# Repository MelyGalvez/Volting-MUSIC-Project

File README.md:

# Volting Music Project
Extension of Volting Music project to a more immersive environnement in Tongji University.

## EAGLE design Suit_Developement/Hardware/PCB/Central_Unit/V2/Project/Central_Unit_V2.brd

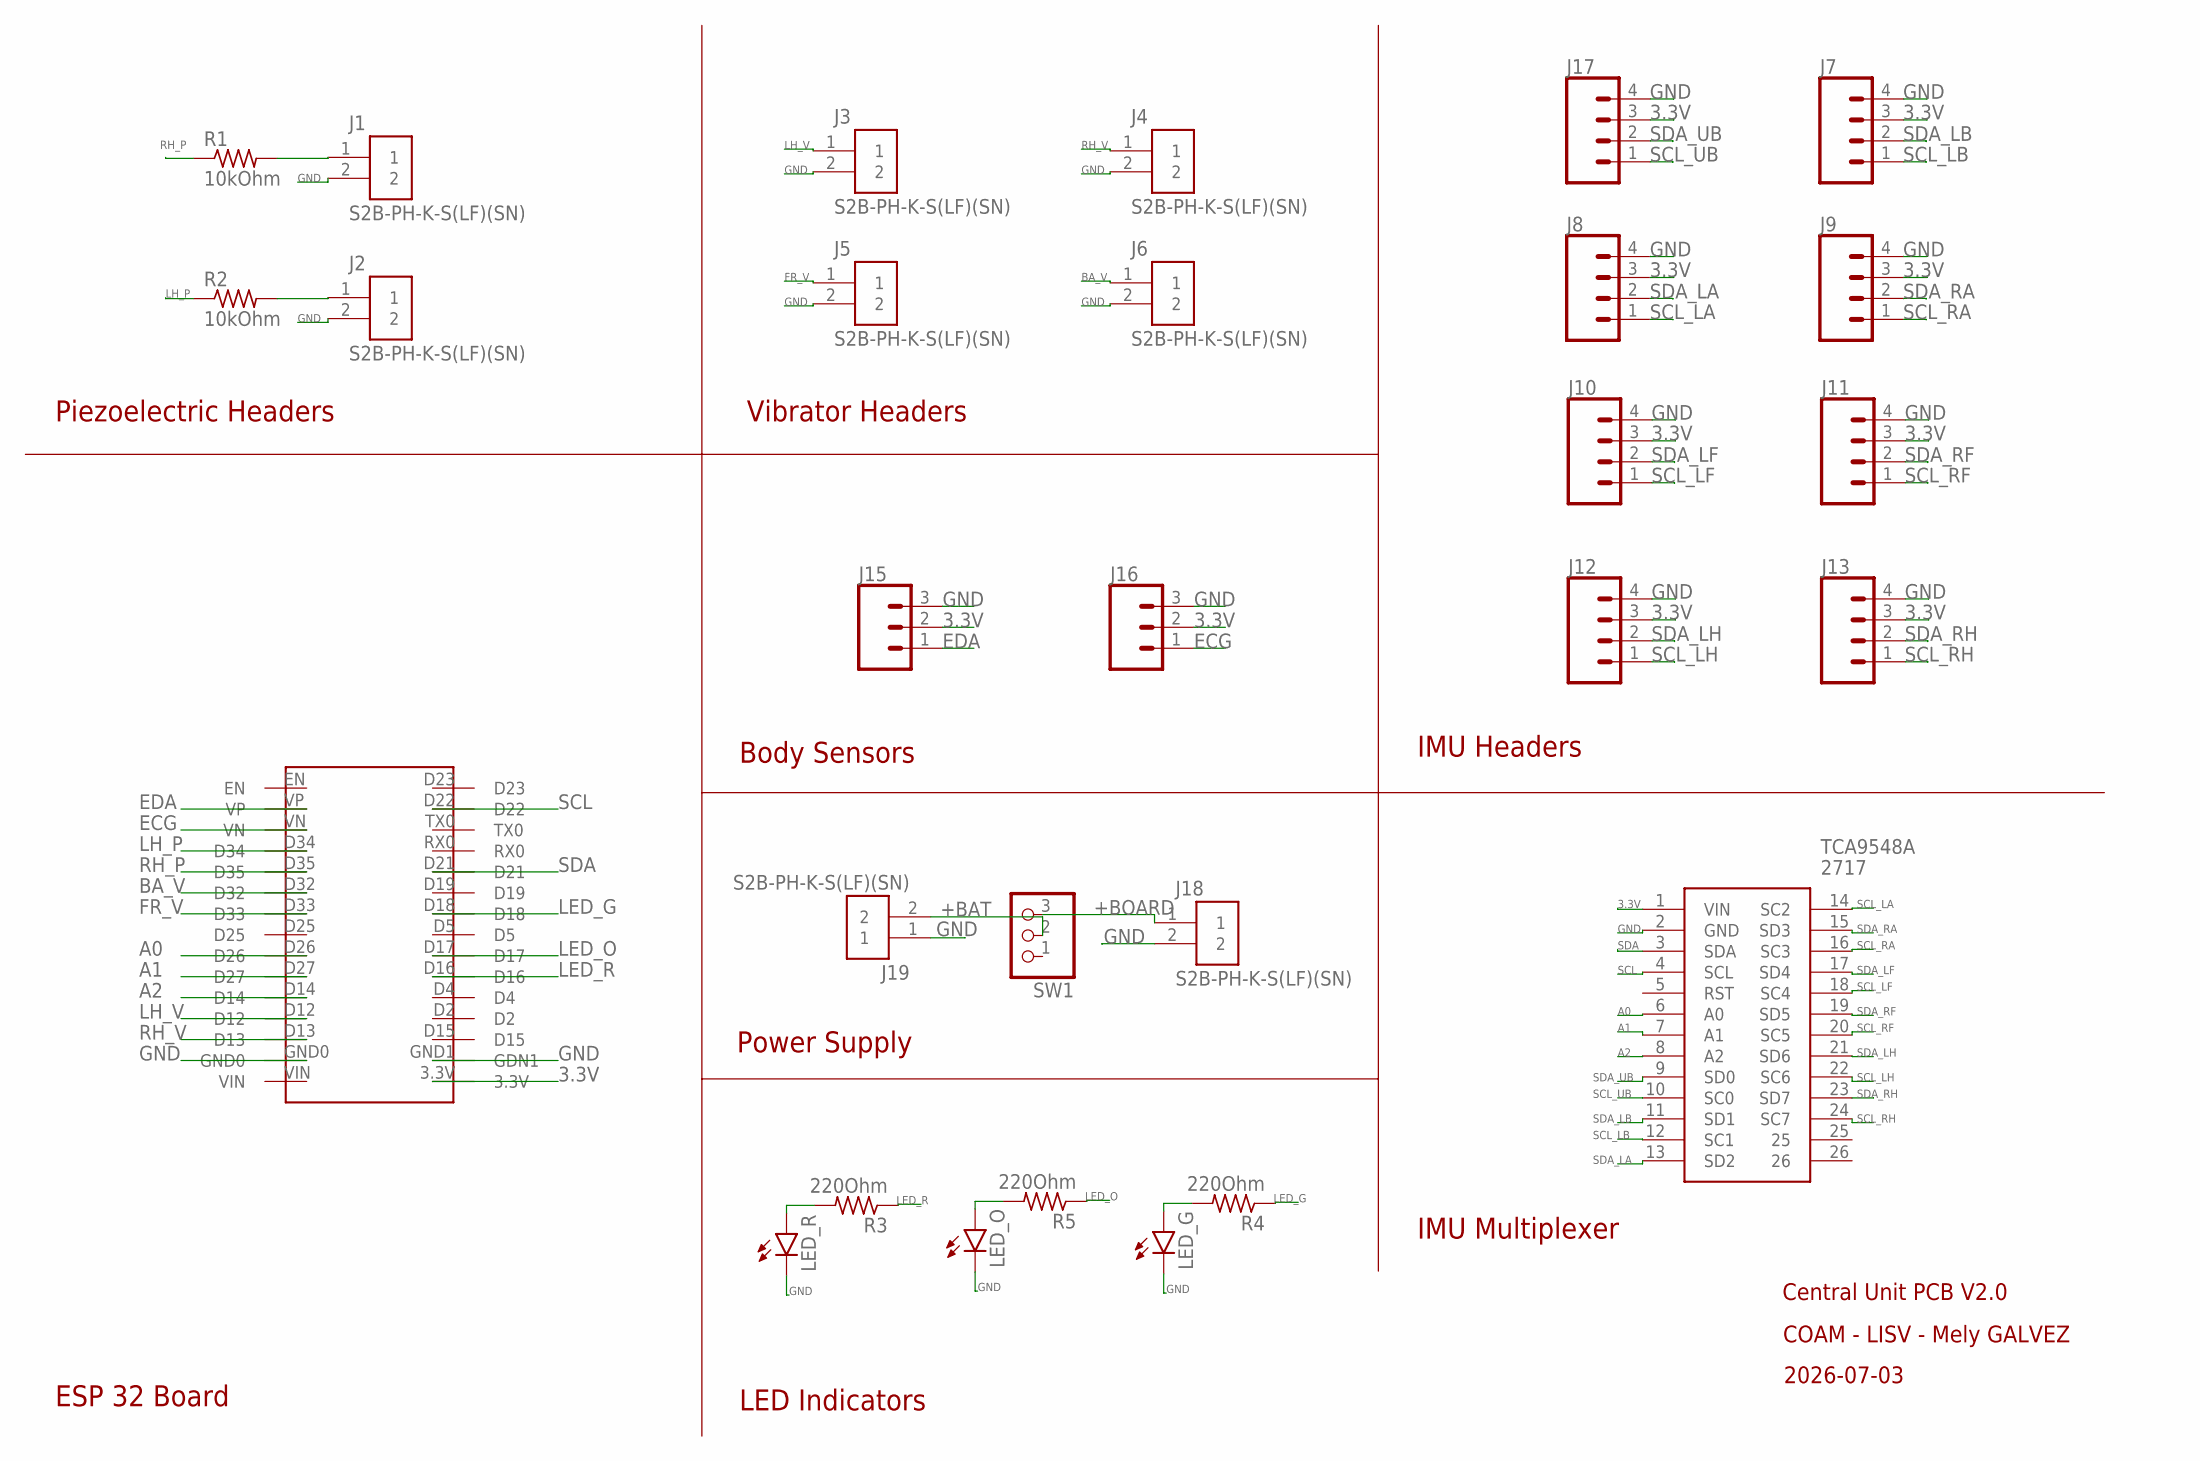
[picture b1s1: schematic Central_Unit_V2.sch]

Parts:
J1, J2, J3, J4, J5, J6, J18, J19: S2B-PH-K-S(LF)(SN)
J7, J8, J9, J10, J11, J12, J13, J17: CONN_04JST-PTH; JST-4-PTH
J15, J16: CONN_03JST-PTH; JST-3-PTH
LED_G: LED3MM
LED_O: LED3MM
LED_R: LED3MM
R1, R2: 10kOhm; 0207/10
R3, R4, R5: 220Ohm; 0207/10
SW1: PINHD-1X3; 1X03
TCA9548A: 2717
U$1: ESP32_WROUM32

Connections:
3.3V: J7.3, J8.3, J9.3, J10.3, J11.3, J12.3, J13.3, J15.2, J16.2, J17.3, TCA9548A.1 (VIN), U$1.3.3V
+BAT: J19.2, SW1.2
+BOARD: J18.1, SW1.3
A0: TCA9548A.6 (A0), U$1.D26
A1: TCA9548A.7 (A1), U$1.D27
A2: TCA9548A.8 (A2), U$1.D14
BA_V: J6.1, U$1.D32
ECG: J16.1, U$1.VN
EDA: J15.1, U$1.VP
FR_V: J5.1, U$1.D33
GND: J1.2, J2.2, J3.2, J4.2, J5.2, J6.2, J7.4, J8.4, J9.4, J10.4, J11.4, J12.4, J13.4, J15.3, J16.3, J17.4, J18.2, J19.1, LED_G.K (C), LED_O.K (C), LED_R.K (C), TCA9548A.2 (GND), U$1.GND0, U$1.GND1 (GDN1)
LED_G: R4.1, U$1.D18
LED_O: R5.1, U$1.D17
LED_R: R3.1, U$1.D16
LH_P: R2.1, U$1.D34
LH_V: J3.1, U$1.D12
unnamed: J1.1, R1.2
unnamed: J2.1, R2.2
unnamed: LED_R.A, R3.2
unnamed: LED_G.A, R4.2
unnamed: LED_O.A, R5.2
RH_P: R1.1, U$1.D35
RH_V: J4.1, U$1.D13
SCL: TCA9548A.4 (SCL), U$1.D22
SCL_LA: J8.1, TCA9548A.14 (SC2)
SCL_LB: J7.1, TCA9548A.12 (SC1)
SCL_LF: J10.1, TCA9548A.18 (SC4)
SCL_LH: J12.1, TCA9548A.22 (SC6)
SCL_RA: J9.1, TCA9548A.16 (SC3)
SCL_RF: J11.1, TCA9548A.20 (SC5)
SCL_RH: J13.1, TCA9548A.24 (SC7)
SCL_UB: J17.1, TCA9548A.10 (SC0)
SDA: TCA9548A.3 (SDA), U$1.D21
SDA_LA: J8.2, TCA9548A.13 (SD2)
SDA_LB: J7.2, TCA9548A.11 (SD1)
SDA_LF: J10.2, TCA9548A.17 (SD4)
SDA_LH: J12.2, TCA9548A.21 (SD6)
SDA_RA: J9.2, TCA9548A.15 (SD3)
SDA_RF: J11.2, TCA9548A.19 (SD5)
SDA_RH: J13.2, TCA9548A.23 (SD7)
SDA_UB: J17.2, TCA9548A.9 (SD0)

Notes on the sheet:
Central Unit PCB V2.0
COAM - LISV - Mely GALVEZ
2026-07-03
LED Indicators
ESP 32 Board
Piezoelectric Headers
Vibrator Headers
IMU Headers
IMU Multiplexer
Power Supply
Body Sensors

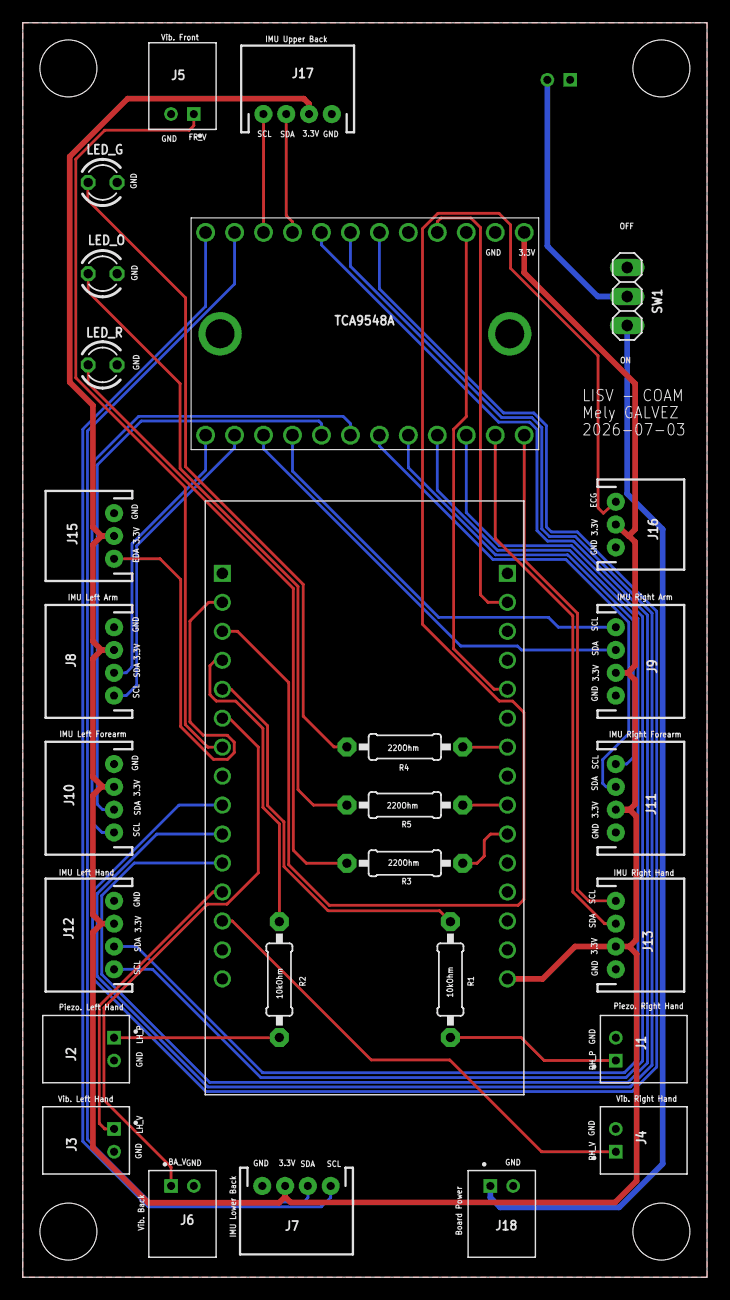
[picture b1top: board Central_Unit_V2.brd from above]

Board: 2 copper layers, 60.0 x 110.0 mm, 29 parts (1 on the bottom side), 41 nets.

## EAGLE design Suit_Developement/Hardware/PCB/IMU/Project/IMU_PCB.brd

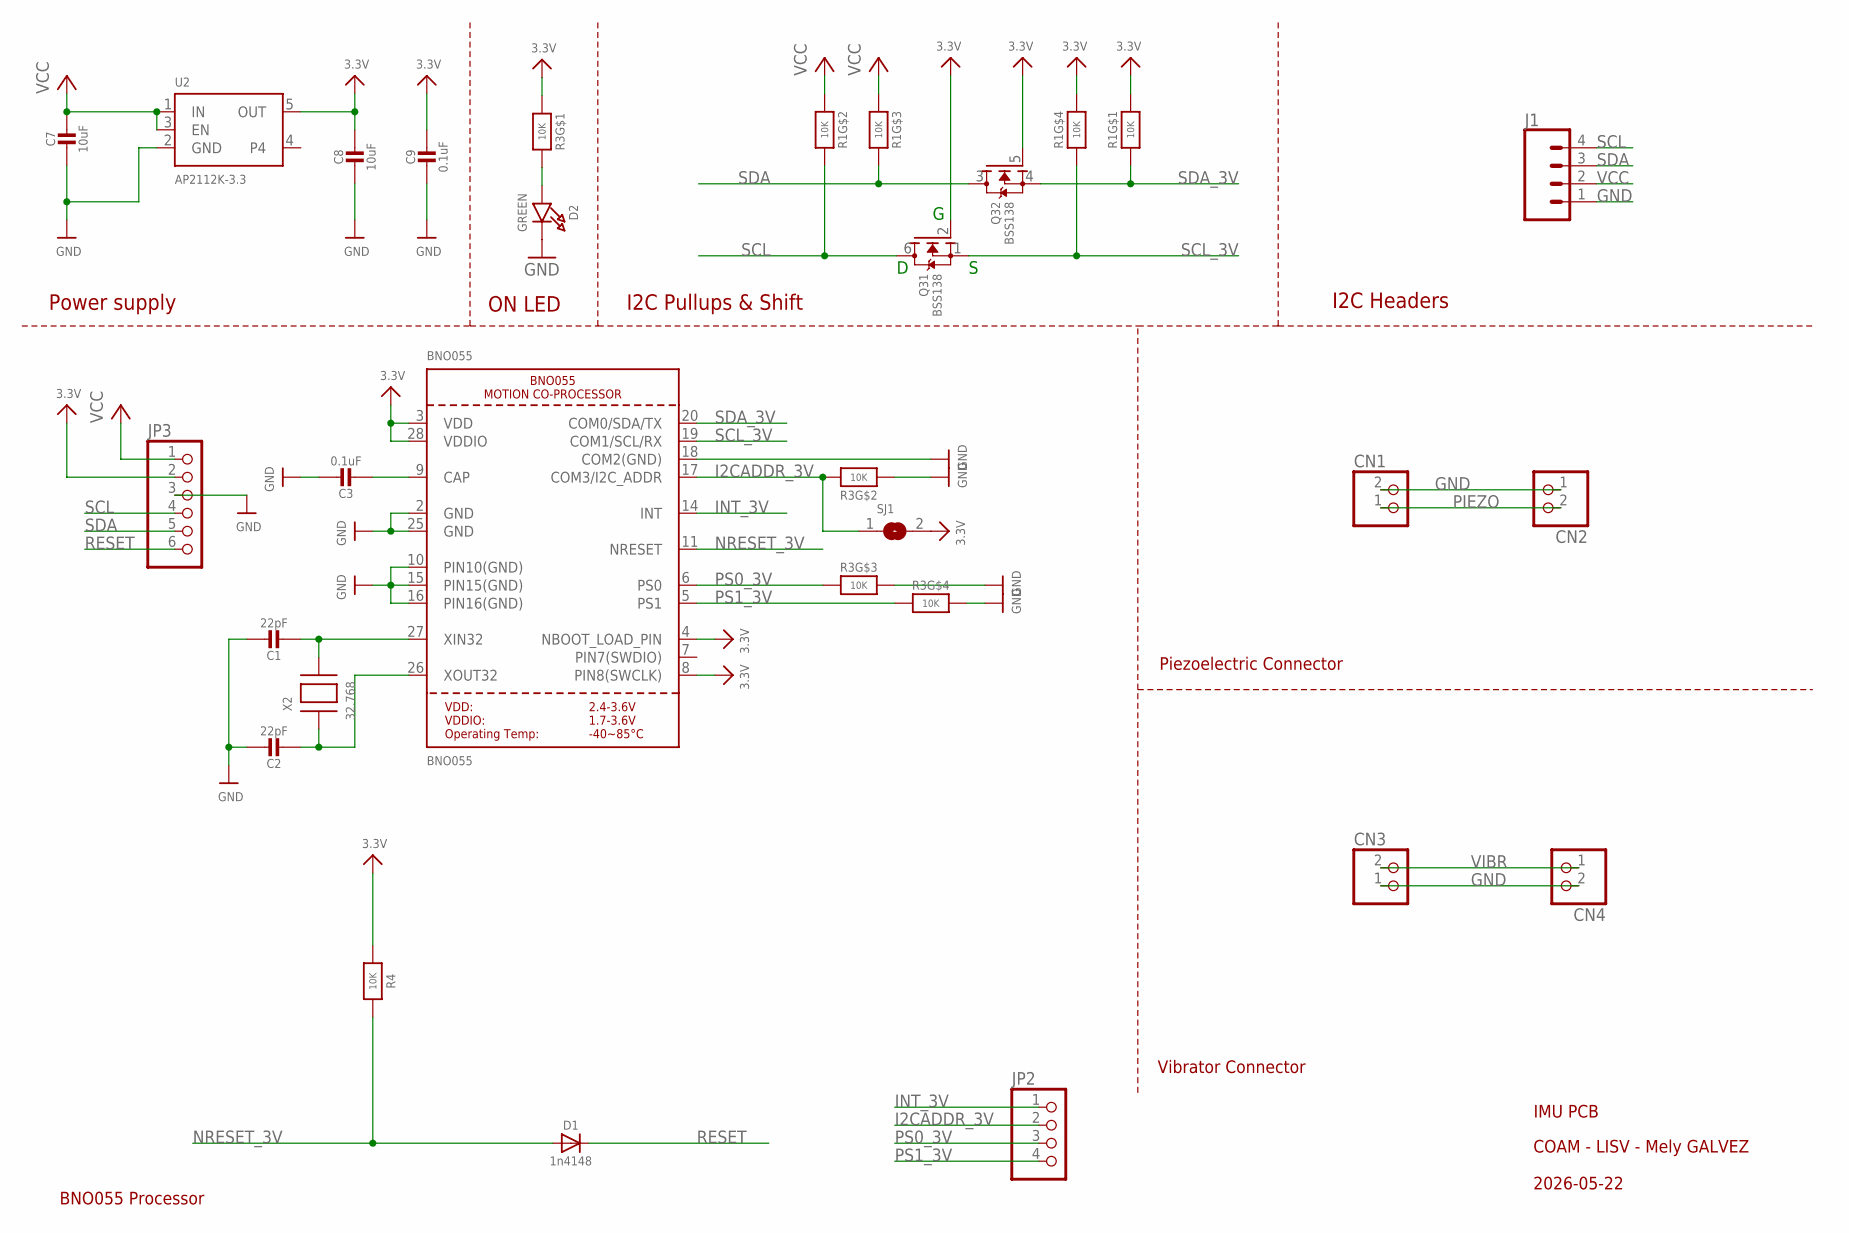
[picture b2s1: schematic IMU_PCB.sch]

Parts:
BNO055: BNO055
C1, C2: 22pF; 0603-NO
C3, C9: 0.1uF; 0603-NO
C7, C8: 10uF; 0805-NO
CN1, CN2, CN3, CN4: JST_2PIN-SMT-RA; JST-PH-2-SMT-RA
D1: 1n4148; SOD-323
D2: GREEN; CHIPLED_0603_NOOUTLINE
J1: CONN_04JST-SMD-LOCKING; JST-4-SMD-1.25MM-LOCKING
JP2: HEADER-1X476MIL; 1X04_ROUND_76
JP3: HEADER-1X670MIL; 1X06_ROUND_70
Q3: BSS138; SOT363
R1, R3: 10K; RESPACK_4X0603
R4: 10K; 0603-NO
SJ1: SOLDERJUMPER; SOLDERJUMPER_ARROW_NOPASTE
U2: AP2112K-3.3; SOT23-5
X2: 32.768; XTAL3215

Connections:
3.3V: BNO055.3 (VDD), BNO055.4 (NBOOT_LOAD_PIN), BNO055.8 (PIN8(SWCLK)), BNO055.28 (VDDIO), C8.1, C9.1, JP3.2, Q3.2 (G), Q3.5 (G), R1.1, R1.4 (1), R3.1, R4.1, SJ1.2, U2.5 (OUT)
GND: BNO055.2 (GND), BNO055.10 (PIN10(GND)), BNO055.15 (PIN15(GND)), BNO055.16 (PIN16(GND)), BNO055.18 (COM2(GND)), BNO055.25 (GND), C1.1, C2.1, C3.1, C7.2, C8.2, C9.2, CN1.2 (1), CN2.1 (2), CN3.1 (2), CN4.2 (1), D2.C, J1.1, JP3.3, R3.2 (1), R3.5 (2), R3.6 (2), U2.2 (GND)
I2CADDR_3V: BNO055.17 (COM3/I2C_ADDR), JP2.2, R3.7 (2), SJ1.1
INT_3V: BNO055.14 (INT), JP2.1
unnamed: BNO055.27 (XIN32), C1.2, X2.P$2
unnamed: BNO055.26 (XOUT32), C2.2, X2.P$1
unnamed: BNO055.9 (CAP), C3.2
unnamed: D2.A, R3.8 (2)
NRESET_3V: BNO055.11 (NRESET), D1.A, R4.2
PIEZO: CN1.1 (2), CN2.2 (1)
PS0_3V: BNO055.6 (PS0), JP2.3, R3.3 (1)
PS1_3V: BNO055.5 (PS1), JP2.4, R3.4 (1)
RESET: D1.C, JP3.6
SCL: J1.4, JP3.4, Q3.6 (D), R1.7 (2)
SCL_3V: BNO055.19 (COM1/SCL/RX), Q3.1 (S), R1.5 (2)
SDA: J1.3, JP3.5, Q3.3 (D), R1.6 (2)
SDA_3V: BNO055.20 (COM0/SDA/TX), Q3.4 (S), R1.8 (2)
VCC: C7.1, J1.2, JP3.1, R1.2 (1), R1.3 (1), U2.1 (IN), U2.3 (EN)
VIBR: CN3.2 (1), CN4.1 (2)

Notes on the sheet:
IMU PCB
COAM - LISV - Mely GALVEZ
2026-05-22
I2C Pullups & Shift
I2C Headers
ON LED
Power supply
BNO055 Processor
Piezoelectric Connector
Vibrator Connector

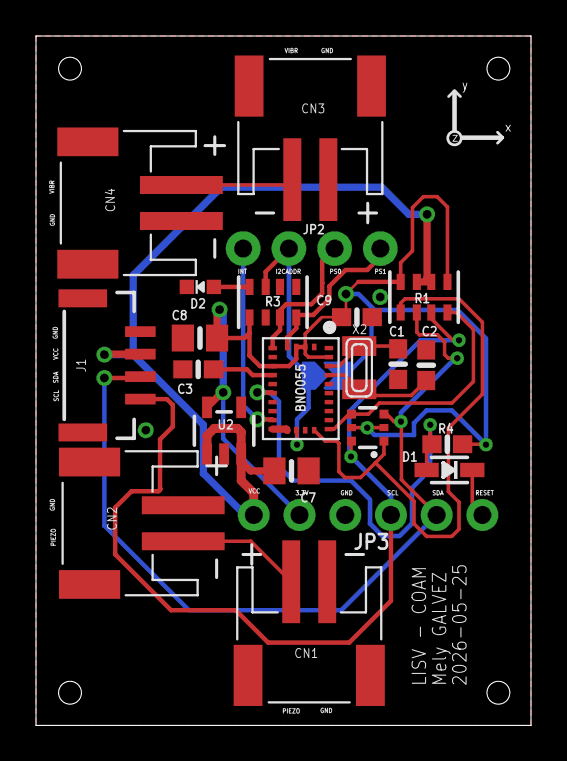
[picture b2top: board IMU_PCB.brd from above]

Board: 2 copper layers, 27.5 x 38.3 mm, 23 parts (1 on the bottom side), 19 nets.

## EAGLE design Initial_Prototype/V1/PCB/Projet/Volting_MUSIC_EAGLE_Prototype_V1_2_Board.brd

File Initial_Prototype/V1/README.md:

# Initial Prototyp - V1

This first version of the prototyp allow the user to create sounds with movements of his own body (hands and chest).

## Prerequisites

### Hardware

- 1 Arduino UNO and it's connection cable.
- 1 IMU GY-85.
- 2 Ultrasound sensors RCW-0001 (as long as you have the ‘TRIG’ and ‘ECHO’ pins, you can use any 4-pin component of your choice).
- 2 4-Pin push-button switches.
- 3 TH LEDs respectively red, yellow and green.
- 5 Security TH resistors of 220 Ohm.
- 2 1-Metre cable leads, male to 4-pin female.
- 2 1-Metre cable leads, male to 3-pin female.
- 1 Breadboard, measuring at least 10 × 10 cm (if you can print your own PCB it's better, the code is in the [Measurement_Device_PCB](https://github.com/MelyGalvez/Volting-MUSIC-Project/tree/main/Initial_Prototype/V1/PCB/Measurement_Device_PCB) file).
- 1 Soldering iron and some tin.

### Software

- Arduino IDE
- Processing-3.5.4

## PCB

Assemble / Solder your board by following the [routing](https://github.com/MelyGalvez/Volting-MUSIC-Project/tree/main/Initial_Prototype/V1/PCB).

## Run code

- Open the [Volting_MUSIC_Arduino_Prototype_V1](https://github.com/MelyGalvez/Volting-MUSIC-Project/tree/main/Initial_Prototype/V1/Codes/Volting_MUSIC_Arduino_Prototype_V1) file.
- Connect your PCB to your machine, select the right COM and board (UNO).
- Download the Arduino code via the IDE.
- You can check the serial monitor to see data sent at the right rate. Do not forget to close this monitor before the next steps. If you don't it will block the COM port.
- Open the [Volting_MUSIC_Processing_Prototype_V1](https://github.com/MelyGalvez/Volting-MUSIC-Project/tree/main/Initial_Prototype/V1/Codes/Volting_MUSIC_Processing_Prototype_V1) file.
- Run the code and enjoy.

## Conclusion

This first version of the prototype works, but is not particularly effective, as the GY-85 IMU is an imprecise sensor. It is therefore difficult to choose the right location for mapping.

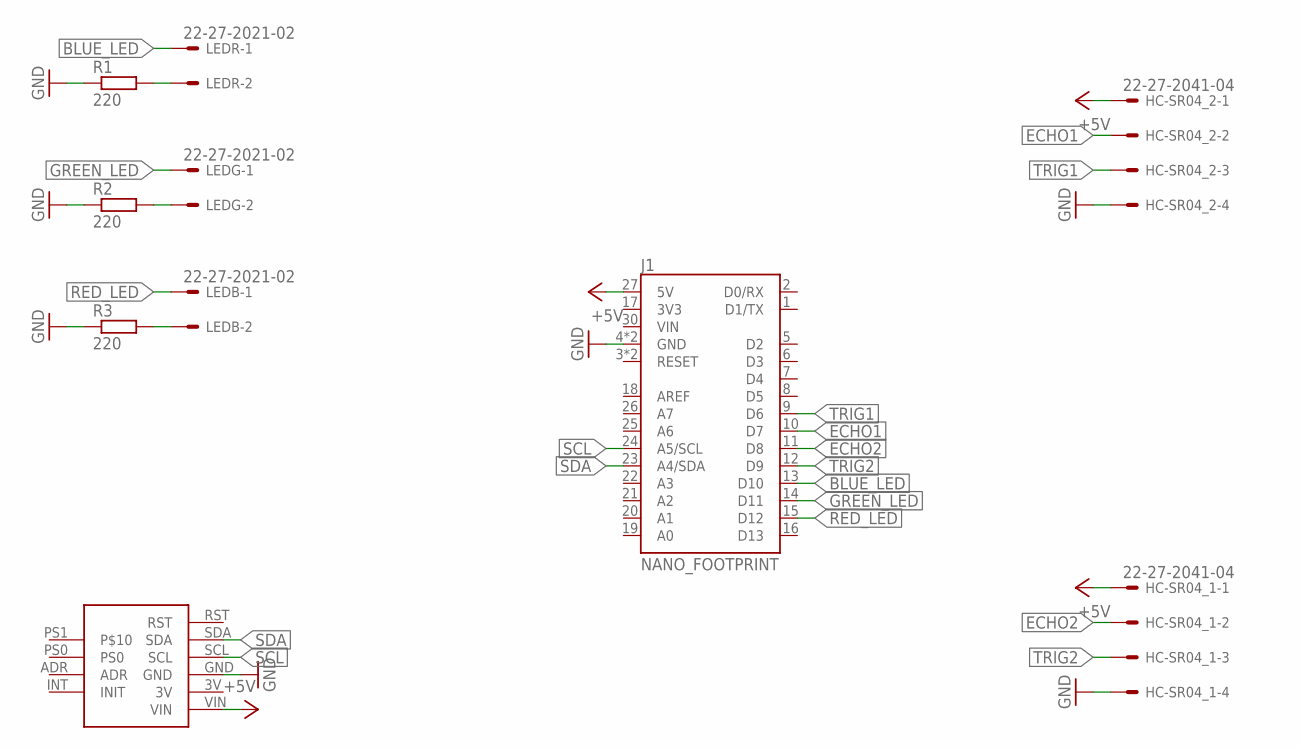
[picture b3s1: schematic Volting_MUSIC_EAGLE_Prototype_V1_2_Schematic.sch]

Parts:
HC-SR04_1, HC-SR04_2: 22-27-2041-04; 6410-04
J1: NANO_FOOTPRINT; NANO
LEDB: 22-27-2021-02; 6410-02
LEDG: 22-27-2021-02; 6410-02
LEDR: 22-27-2021-02; 6410-02
R1, R2, R3: 220; M1206
U$1: BNO055

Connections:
+5V: HC-SR04_1.1, HC-SR04_2.1, J1.27 (5V), U$1.VIN
BLUE_LED: J1.13 (D10), LEDR.1
ECHO1: HC-SR04_2.2, J1.10 (D7)
ECHO2: HC-SR04_1.2, J1.11 (D8)
GND: HC-SR04_1.4, HC-SR04_2.4, J1.4 (GND), J1.29 (GND), R1.1, R2.1, R3.1, U$1.GND
GREEN_LED: J1.14 (D11), LEDG.1
unnamed: LEDR.2, R1.2
unnamed: LEDG.2, R2.2
unnamed: LEDB.2, R3.2
RED_LED: J1.15 (D12), LEDB.1
SCL: J1.24 (A5/SCL), U$1.SCL
SDA: J1.23 (A4/SDA), U$1.SDA
TRIG1: HC-SR04_2.3, J1.9 (D6)
TRIG2: HC-SR04_1.3, J1.12 (D9)

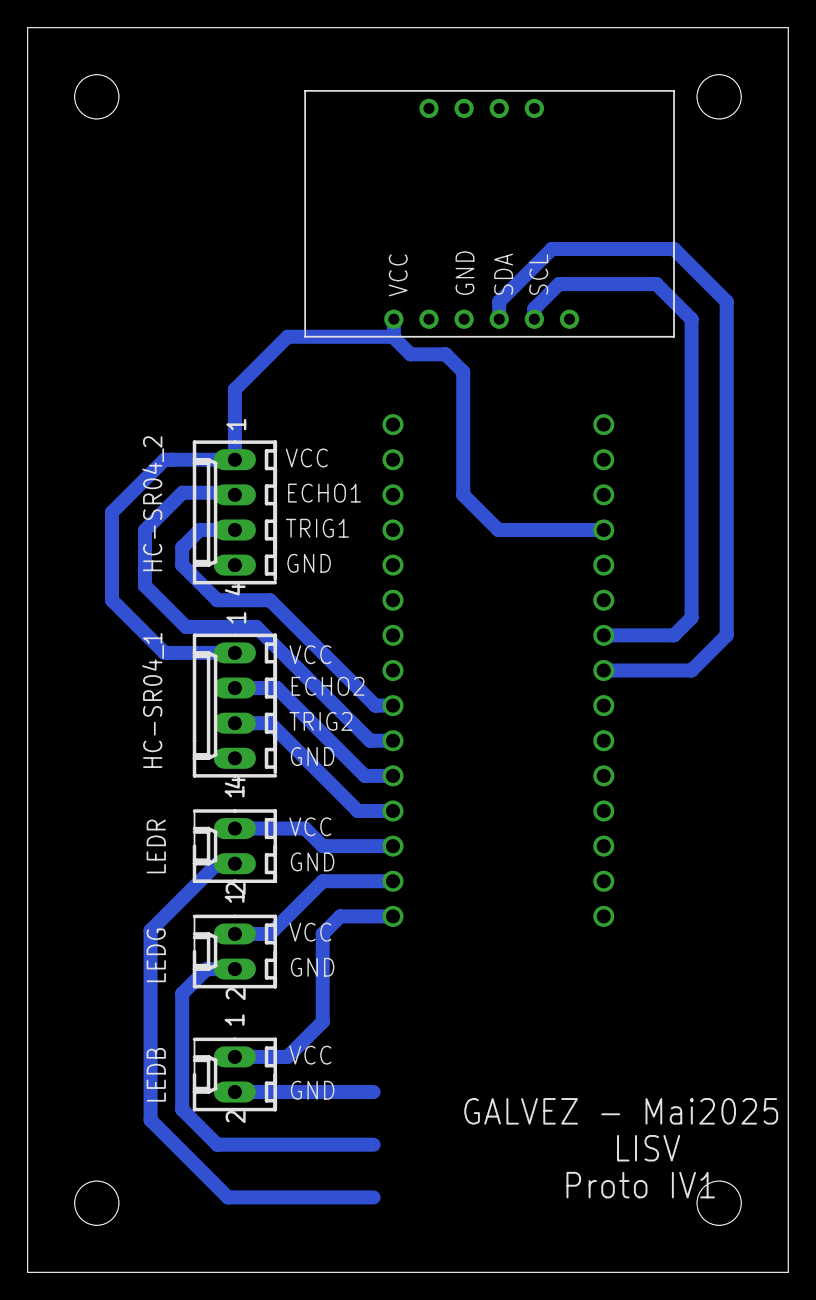
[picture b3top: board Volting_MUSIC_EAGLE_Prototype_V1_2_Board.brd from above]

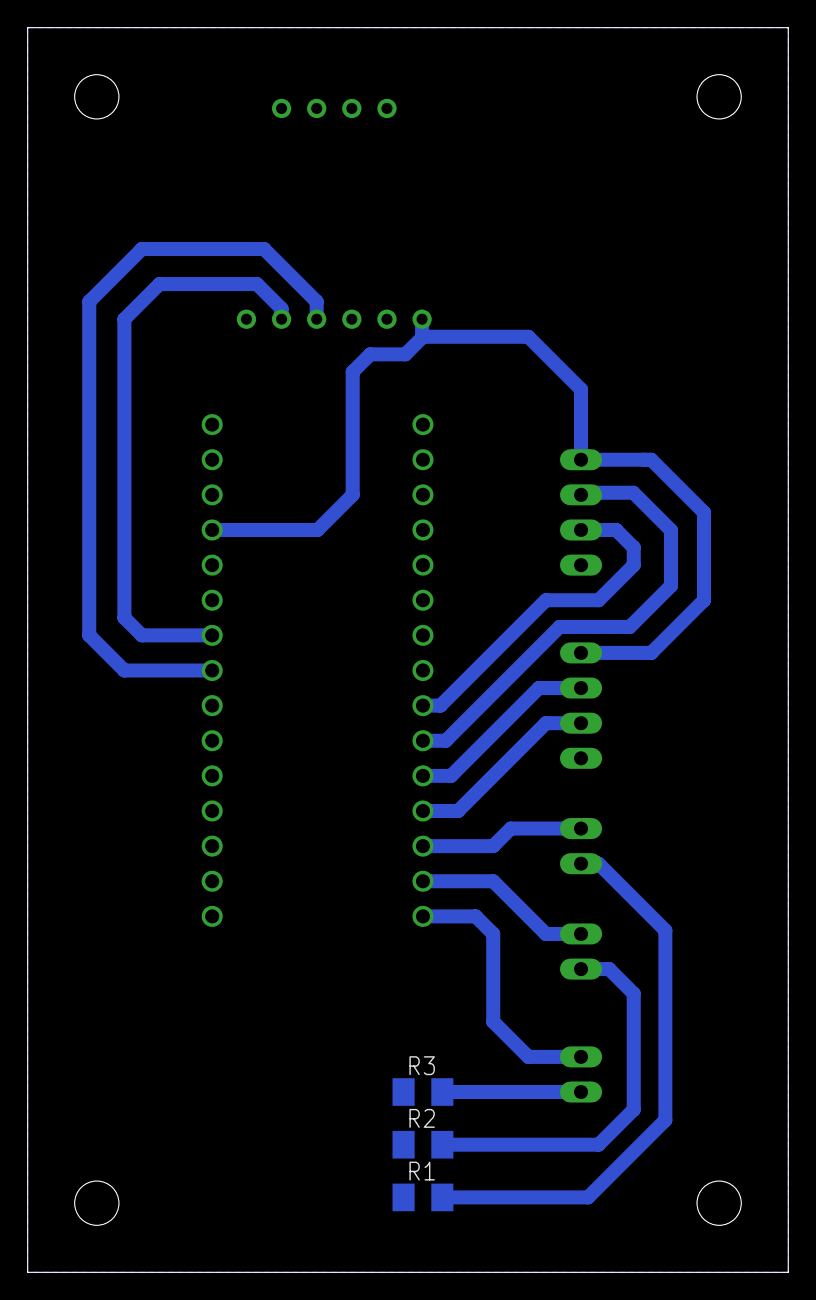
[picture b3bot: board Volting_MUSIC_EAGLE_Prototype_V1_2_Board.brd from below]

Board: 2 copper layers, 55.0 x 90.0 mm, 10 parts (3 on the bottom side), 14 nets.

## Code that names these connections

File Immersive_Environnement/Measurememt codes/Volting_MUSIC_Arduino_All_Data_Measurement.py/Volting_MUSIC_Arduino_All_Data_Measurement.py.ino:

#include <Wire.h>

// ---------- ADXL345 ----------
#define ADXL345 0x53
#define DATAX0 0x32

// ---------- ITG3200 ----------
#define ITG3200 0x68

// ---------- HMC5883L ----------
#define HMC5883L 0x1E

// ---------- Ultrason ----------
#define TRIG1 2
#define ECHO1 3
#define TRIG2 4
#define ECHO2 5

// ---------- Boutons ----------
#define BTN1 6
#define BTN2 7

// ---------- LEDs ----------
#define BLUE_LED 8
#define GREEN_LED 9
#define RED_LED 10

void setup() {
  Serial.begin(115200);
  Wire.begin();

  // LEDs
  pinMode(BLUE_LED, OUTPUT);
  pinMode(GREEN_LED, OUTPUT);
  pinMode(RED_LED, OUTPUT);

  digitalWrite(BLUE_LED, HIGH); // init

  // Ultrason
  pinMode(TRIG1, OUTPUT);
  pinMode(ECHO1, INPUT);
  pinMode(TRIG2, OUTPUT);
  pinMode(ECHO2, INPUT);

  // Boutons (pull-down externe)
  pinMode(BTN1, INPUT);
  pinMode(BTN2, INPUT);

  // Init ADXL345
  writeReg(ADXL345, 0x2D, 0x08);
  writeReg(ADXL345, 0x31, 0x08);

  // Init HMC5883L
  writeReg(HMC5883L, 0x00, 0x70);
  writeReg(HMC5883L, 0x01, 0x20);
  writeReg(HMC5883L, 0x02, 0x00);

  digitalWrite(GREEN_LED, HIGH);
  digitalWrite(BLUE_LED, LOW);
}

// ---------- LOOP ----------
void loop() {

  // ---------- IMU ----------
  int16_t ax, ay, az;
  readAccel(ax, ay, az);

  int16_t gx, gy, gz;
  readGyro(gx, gy, gz);

  int16_t mx, my, mz;
  readMag(mx, my, mz);

  // ---------- ULTRASON ----------
  long d1 = measureDistance(TRIG1, ECHO1);
  long d2 = measureDistance(TRIG2, ECHO2);

  // ---------- BOUTONS ----------
  bool b1 = digitalRead(BTN1);
  bool b2 = digitalRead(BTN2);

  // ---------- LEDs ----------
  digitalWrite(BLUE_LED, b1);
  digitalWrite(GREEN_LED, b2);
  digitalWrite(RED_LED, b1 && b2);

  // ---------- SERIAL OUTPUT ----------
  Serial.print("ACC: ");
  Serial.print(ax); Serial.print(", ");
  Serial.print(ay); Serial.print(", ");
  Serial.println(az);

  Serial.print("GYRO: ");
  Serial.print(gx); Serial.print(", ");
  Serial.print(gy); Serial.print(", ");
  Serial.println(gz);

  Serial.print("MAG: ");
  Serial.print(mx); Serial.print(", ");
  Serial.print(my); Serial.print(", ");
  Serial.println(mz);

  Serial.print("D1: "); Serial.println(d1);
  Serial.print("D2: "); Serial.println(d2);

  Serial.print("BTN: ");
  Serial.print(b1); Serial.print(", ");
  Serial.println(b2);

  Serial.println("---");

  delay(100);
}

// ---------- ULTRASON ----------
long measureDistance(int trig, int echo) {
  digitalWrite(trig, LOW);
  delayMicroseconds(2);
  digitalWrite(trig, HIGH);
  delayMicroseconds(10);
  digitalWrite(trig, LOW);

  long duration = pulseIn(echo, HIGH, 30000);
  long distance = (duration * 0.0343) / 2;
  return constrain(distance, 0, 200);
}

// ---------- ACCEL ----------
void readAccel(int16_t &x, int16_t &y, int16_t &z) {
  Wire.beginTransmission(ADXL345);
  Wire.write(DATAX0);
  Wire.endTransmission();
  Wire.requestFrom(ADXL345, 6);

  uint8_t b[6];
  for (int i = 0; i < 6; i++) b[i] = Wire.read();

  x = (b[1] << 8) | b[0];
  y = (b[3] << 8) | b[2];
  z = (b[5] << 8) | b[4];
}

// ---------- GYRO ----------
void readGyro(int16_t &x, int16_t &y, int16_t &z) {
  Wire.beginTransmission(ITG3200);
  Wire.write(0x1D);
  Wire.endTransmission();
  Wire.requestFrom(ITG3200, 6);

  x = Wire.read() << 8 | Wire.read();
  y = Wire.read() << 8 | Wire.read();
  z = Wire.read() << 8 | Wire.read();
}

// ---------- MAG ----------
void readMag(int16_t &x, int16_t &y, int16_t &z) {
  Wire.beginTransmission(HMC5883L);
  Wire.write(0x03);
  Wire.endTransmission();
  Wire.requestFrom(HMC5883L, 6);

  x = Wire.read() << 8 | Wire.read();
  z = Wire.read() << 8 | Wire.read();
  y = Wire.read() << 8 | Wire.read();
}

// ---------- I2C WRITE ----------
void writeReg(byte addr, byte reg, byte val) {
  Wire.beginTransmission(addr);
  Wire.write(reg);
  Wire.write(val);
  Wire.endTransmission();
}

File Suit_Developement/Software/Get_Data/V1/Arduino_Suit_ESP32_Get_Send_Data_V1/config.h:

#pragma once


// ================================================
// CONFIG.h
// ================================================


// --------------- Pin configuration --------------


#define SDA_PIN             21
#define SCL_PIN             22

#define PIEZO_LEFT_PIN      34
#define PIEZO_RIGHT_PIN     35

#define LED_R_PIN           16
#define LED_O_PIN           17
#define LED_G_PIN           18

#define VIB_LEFT_PIN        12
#define VIB_RIGHT_PIN       13


// --------------- I2C configuration --------------


#define TCA9548A_ADDR       0x70


// --------------- IMU configuration --------------


#define NUM_IMUS            8
#define FIRST_IMU_CHANNEL   8


// -------------- Wifi configuration --------------


constexpr char WIFI_SSID[] = "ESP32_Test";
constexpr char WIFI_PASSWORD[] = "12345678";

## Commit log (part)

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2026-04-13 Measurements code
2026-04-13 Prototype's code uploading
2026-04-13 Rename stl file
2026-04-15 New PCB
2026-04-15 PCB Update
2026-04-21 Measurements codes
2026-04-21 New meassurement code importation
2026-04-23 Updates of P1 Arduino code
2026-04-23 Updates and modifications
2026-04-23 Readme update
2026-04-23 Measurement codes updates
2026-05-21 Suit Dev
2026-05-25 IMU PCB Design
2026-05-26 IMU Gerber files
2026-05-27 Update IMU PCB and Upload Central Unit PCB
2026-05-29 PCB Design
2026-06-30 Beginning of software

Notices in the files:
parts and their libraries:
SparkFun-Boards: Licensing: Creative Commons ShareAlike 4.0 International - https://creativecommons.org/licenses/by-sa/4.0
microbuilder: This work is placed in the public domain, and may be freely used for commercial and non-commercial work with the following conditions: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
